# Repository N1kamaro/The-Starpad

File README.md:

# The-Starpad
Hello!! this is starpad , my own macropad!

Above, you'll find two ways to access the PCB: the complete KiCad project files and a folder containing information about each part of the PCB!

Thank you so much for following and being part of the process. This is the first and only macropad I've ever made, called the Starpad!

Bye bye!! 👋⭐️

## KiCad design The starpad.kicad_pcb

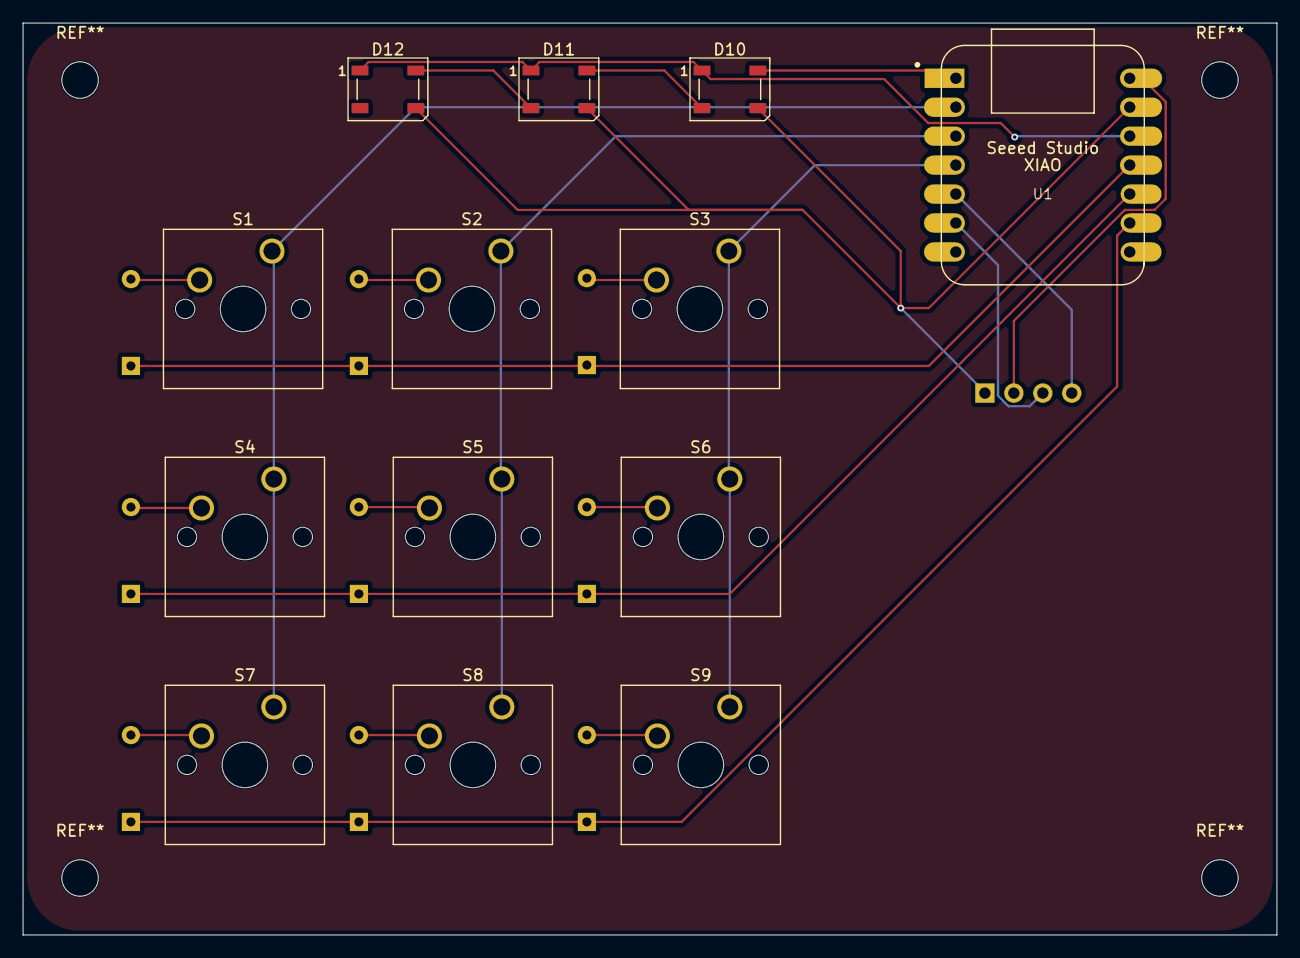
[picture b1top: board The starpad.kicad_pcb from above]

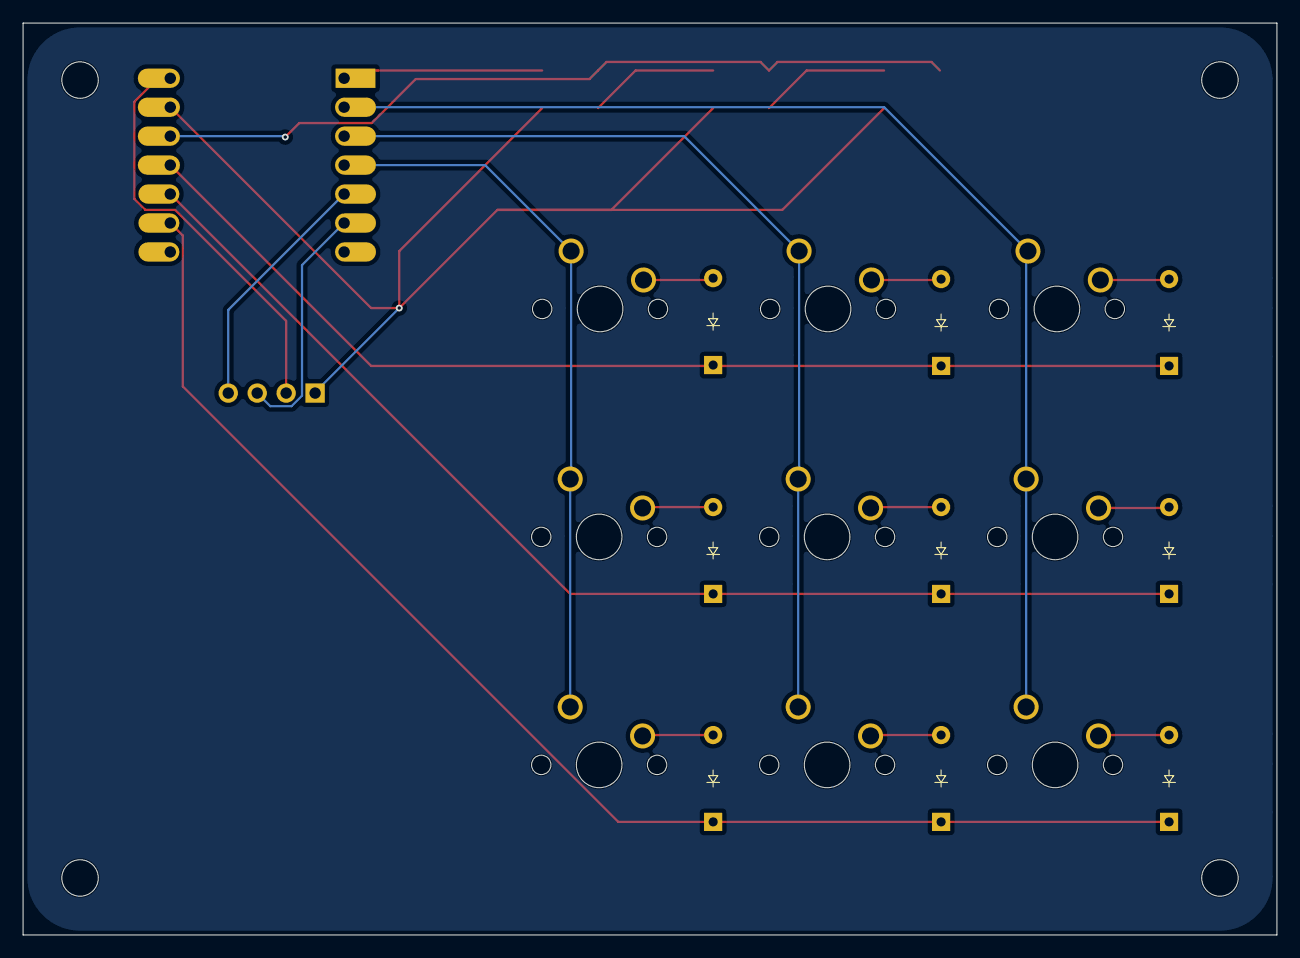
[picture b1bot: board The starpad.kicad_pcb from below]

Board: 2 copper layers, 110.0 x 80.0 mm, 23 parts (9 on the bottom side), 23 nets.

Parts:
D1, D2, D3, D4, D5, D6, D7, D8, D9: Diode_DO-35
D10, D11, D12: WS2812B; LED_WS2812B_PLCC4_5.0x5.0mm_P3.2mm
J1: OLED_128x32
S1, S2, S3, S4, S5, S6, S7, S8, S9: SW_Cherry_MX_1.00u_PCB
U1: MOUDLE-SEEEDUINO-XIAO; XIAO-Generic-Hybrid-14P-2.54-21X17.8MM

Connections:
Coluna 1: S1.1, S4.1, S7.1, U1.2 (PA4_A1_D1)
Coluna 2: S2.1, S5.1, S8.1, U1.3 (PA10_A2_D2)
Coluna 3: S3.1, S6.1, S9.1, U1.4 (PA11_A3_D3)
GND: D10.3 (VSS), D11.3 (VSS), D12.3 (VSS), J1.1 (GND), U1.13 (GND)
Linha 1: D1.1 (K), D2.1 (K), D3.1 (K), U1.11 (PA6_A10_D10_MOSI)
Linha 2: D4.1 (K), D5.1 (K), D6.1 (K), U1.10 (PA5_A9_D9_MISO)
Linha 3: D7.1 (K), D8.1 (K), D9.1 (K), U1.9 (PA7_A8_D8_SCK)
unnamed: D1.2 (A), S1.2
unnamed: D2.2 (A), S2.2
unnamed: D3.2 (A), S3.2
unnamed: D4.2 (A), S4.2
unnamed: D5.2 (A), S5.2
unnamed: D6.2 (A), S6.2
unnamed: D7.2 (A), S7.2
unnamed: D8.2 (A), S8.2
unnamed: D9.2 (A), S9.2
unnamed: D10.2 (DOUT), D11.4 (DIN)
unnamed: D11.2 (DOUT), D12.4 (DIN)
RBG: D10.4 (DIN), U1.1 (PA02_A0_D0)
SCL display: J1.3 (SCL), U1.6 (PA9_A5_D5_SCL)
SDA display: J1.4 (SDA), U1.5 (PA8_A4_D4_SDA)
Vcc: D10.1 (VDD), D11.1 (VDD), D12.1 (VDD), U1.12 (3V3)
Vcc5: J1.2 (VCC), U1.14 (5V)

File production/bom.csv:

Designator,Footprint,Quantity,Value,LCSC Part #
"D1, D2, D3, D4, D5, D6, D7, D8, D9",Diode_DO-35,9,~,
"D10, D11, D12",LED_WS2812B_PLCC4_5.0x5.0mm_P3.2mm,3,WS2812B,
J1,OLED_128x32,1,OLED_128x32,
"S1, S2, S3, S4, S5, S6, S7, S8, S9",SW_Cherry_MX_1.00u_PCB,9,~,
U1,XIAO-Generic-Hybrid-14P-2.54-21X17.8MM,1,MOUDLE-SEEEDUINO-XIAO,
